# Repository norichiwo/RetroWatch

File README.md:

# RetroWatch

PCB file creation = KiCAD : Version: 8.0.1

Firmware creation = STM32CubeIDE : Version: 1.15.1

Details are shown in following blog pages ( Only in Japanese)

https://norichiwo.hatenablog.com/entry/2024/11/10/233512

https://norichiwo.hatenablog.com/entry/2024/11/17/223525

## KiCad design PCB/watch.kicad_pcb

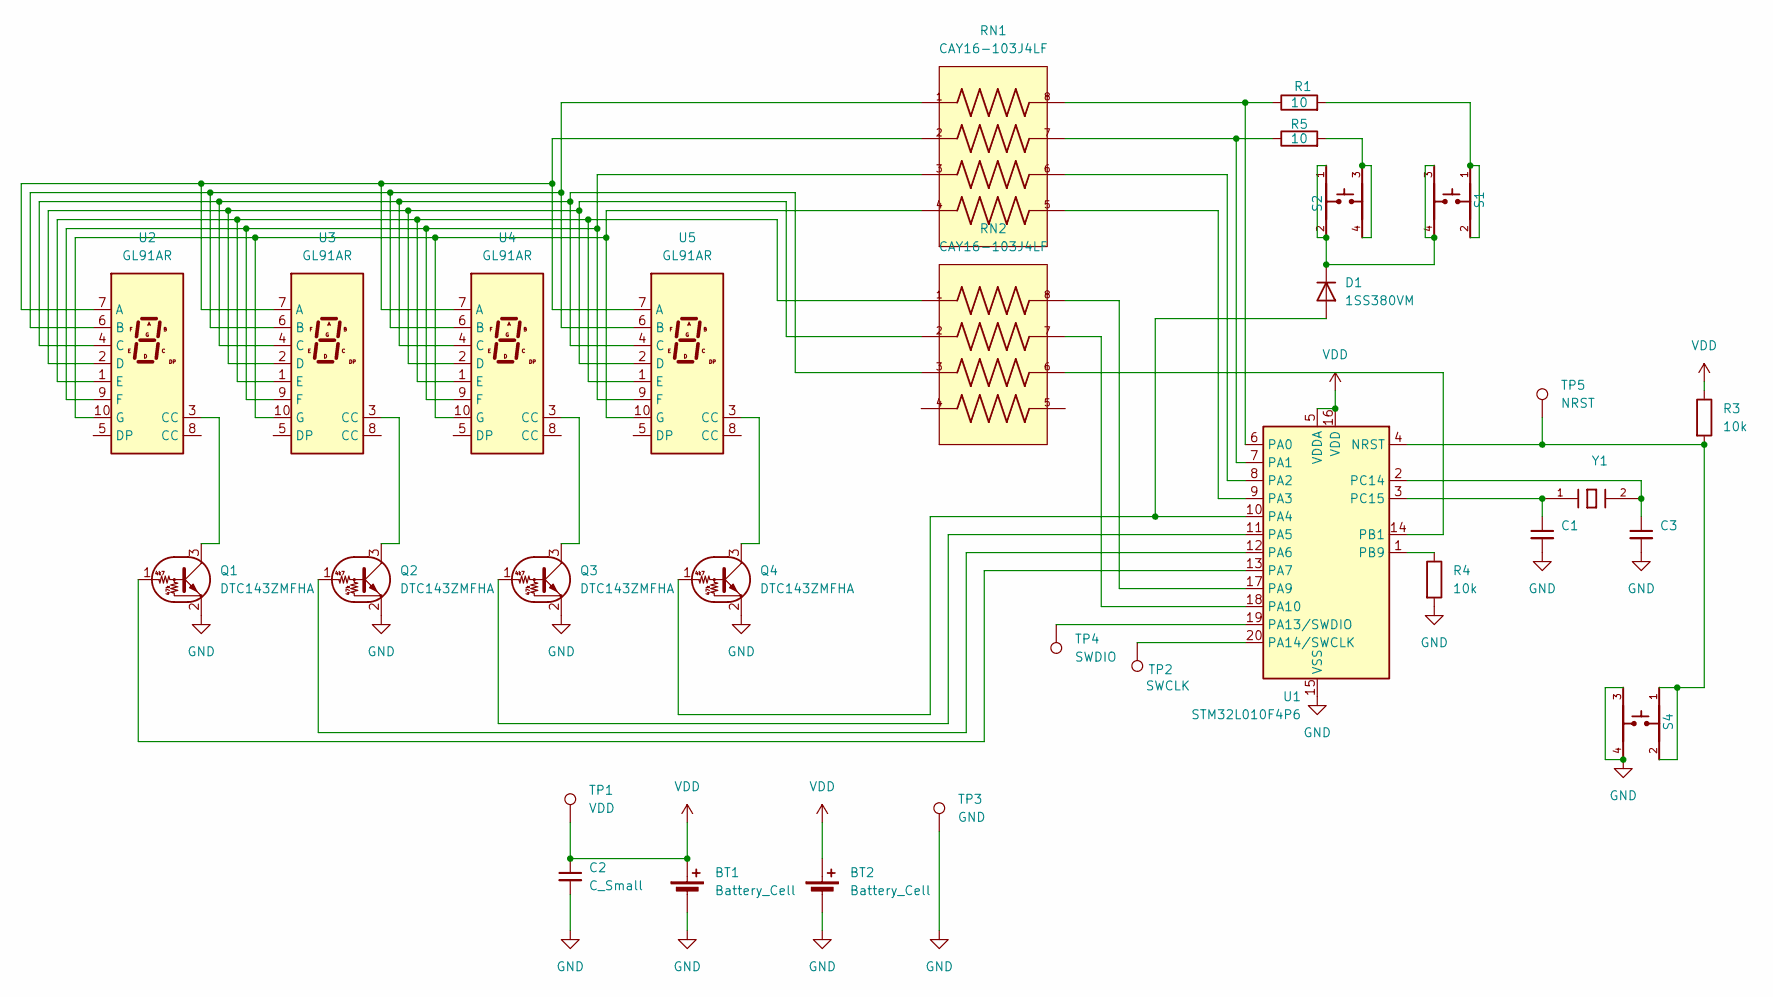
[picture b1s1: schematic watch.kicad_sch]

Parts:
BT1: Battery_Cell; BatteryHolder_Keystone_1058_1x2032
BT2: Battery_Cell; Battery_CH224-2032
C1, C2, C3: C_Small; C_0603_1608Metric
D1: 1SS380VM; D_SOD-323F
Q1, Q2, Q3, Q4: DTC143ZMFHA; SOT-723
R1, R5: 10; R_0603_1608Metric
R3, R4: 10k; R_0603_1608Metric
RN1, RN2: CAY16-103J4LF; RESCAF80P320X160X60-8N
S1, S2, S4: SKRPACE010; SW_SKRPACE010
TP1: VDD; TestPoint_THTPad_D1.1mm_Drill0.7mm
TP2: SWCLK; TestPoint_THTPad_D1.1mm_Drill0.7mm
TP3: GND; TestPoint_THTPad_D1.1mm_Drill0.7mm
TP4: SWDIO; TestPoint_THTPad_D1.1mm_Drill0.7mm
TP5: NRST; TestPoint_THTPad_D1.1mm_Drill0.7mm
U1: STM32L010F4P6; TSSOP-20_4.4x6.5mm_P0.65mm
U2, U3, U4, U5: GL91AR
Y1: FC-135_32.7680KA-A0; XTAL_FC-135_32.7680KA-A0

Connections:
GND: BT1.2 (-), BT2.2 (-), C1.2, C2.2, C3.2, Q1.2 (E), Q2.2 (E), Q3.2 (E), Q4.2 (E), R4.2, S4.3, S4.4, TP3.1, U1.15 (VSS)
unnamed: D1.2 (A), Q4.1 (B), U1.10 (PA4)
unnamed: D1.1 (K), S1.3, S1.4, S2.1, S2.2
unnamed: Q1.1 (B), U1.13 (PA7)
unnamed: Q1.3 (C), U2.3 (CC)
unnamed: Q2.1 (B), U1.12 (PA6)
unnamed: Q2.3 (C), U3.3 (CC)
unnamed: Q3.1 (B), U1.11 (PA5)
unnamed: Q3.3 (C), U4.3 (CC)
unnamed: Q4.3 (C), U5.3 (CC)
unnamed: R1.2, S1.1, S1.2
unnamed: R5.2, S2.3, S2.4
unnamed: R3.2, S4.1, S4.2, TP5.1, U1.4 (NRST)
unnamed: R1.1, RN1.8, U1.6 (PA0)
unnamed: R5.1, RN1.7, U1.7 (PA1)
unnamed: RN1.6, U1.8 (PA2)
unnamed: RN1.5, U1.9 (PA3)
unnamed: RN2.8, U1.17 (PA9)
unnamed: RN2.7, U1.18 (PA10)
unnamed: TP4.1, U1.19 (PA13/SWDIO)
unnamed: TP2.1, U1.20 (PA14/SWCLK)
unnamed: RN2.6, U1.14 (PB1)
unnamed: R4.1, U1.1 (PB9)
unnamed: C3.1, U1.2 (PC14), Y1.2
unnamed: C1.1, U1.3 (PC15), Y1.1
unnamed: RN1.2, U2.7 (A), U3.7 (A), U4.7 (A), U5.7 (A)
unnamed: RN1.1, U2.6 (B), U3.6 (B), U4.6 (B), U5.6 (B)
unnamed: RN2.3, U2.4 (C), U3.4 (C), U4.4 (C), U5.4 (C)
unnamed: RN2.2, U2.2 (D), U3.2 (D), U4.2 (D), U5.2 (D)
unnamed: RN2.1, U2.1 (E), U3.1 (E), U4.1 (E), U5.1 (E)
unnamed: RN1.3, U2.9 (F), U3.9 (F), U4.9 (F), U5.9 (F)
unnamed: RN1.4, U2.10 (G), U3.10 (G), U4.10 (G), U5.10 (G)
VDD: BT1.1 (+), BT2.1 (+), C2.1, R3.1, TP1.1, U1.5 (VDDA), U1.16 (VDD)

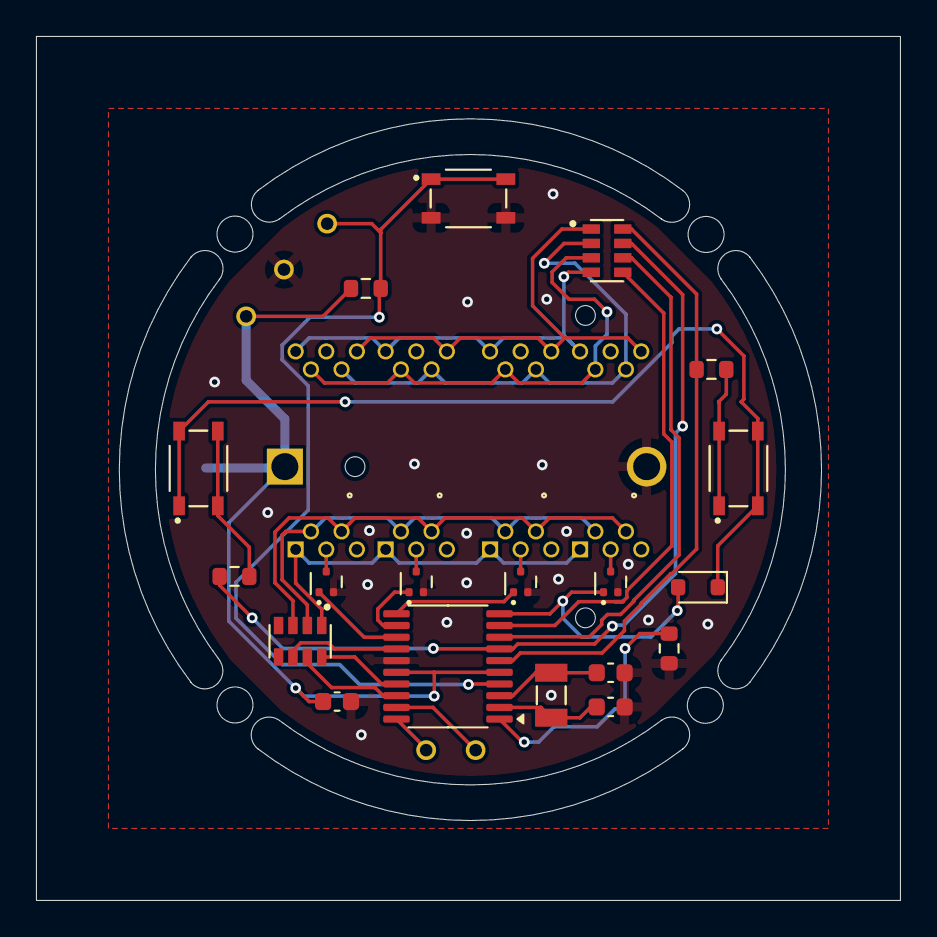
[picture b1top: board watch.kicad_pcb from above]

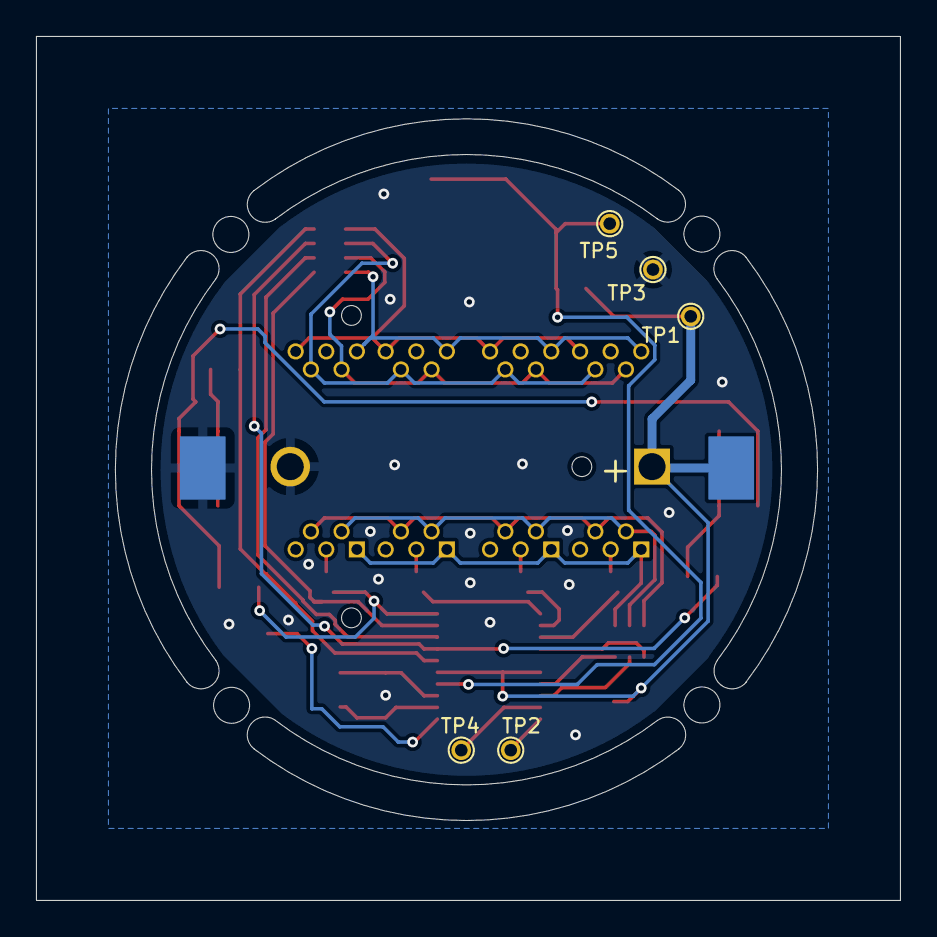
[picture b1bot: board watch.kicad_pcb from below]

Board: 2 copper layers, 48.0 x 48.0 mm, 30 parts (7 on the bottom side), 33 nets.

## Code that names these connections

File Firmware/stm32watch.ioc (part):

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Mcu.Name=STM32L010F4Px
Mcu.Package=TSSOP20
Mcu.UserName=STM32L010F4Px
PA0-CK_IN.GPIOParameters=GPIO_Speed,GPIO_PuPd,GPIO_Label,GPIO_ModeDefaultOutputPP
PA0-CK_IN.GPIO_Label=SEGB
PA0-CK_IN.GPIO_ModeDefaultOutputPP=GPIO_MODE_OUTPUT_PP
PA0-CK_IN.GPIO_PuPd=GPIO_NOPULL
PA0-CK_IN.GPIO_Speed=GPIO_SPEED_FREQ_LOW
PA0-CK_IN.Signal=GPIO_Output
PA1.GPIOParameters=GPIO_Speed,GPIO_Label
PA1.GPIO_Label=SEGA
PA1.GPIO_Speed=GPIO_SPEED_FREQ_LOW
PA1.Signal=GPIO_Output
PA10.GPIOParameters=GPIO_Label
PA10.GPIO_Label=SEGD
PA10.Signal=GPIO_Output
PA13.Mode=Serial_Wire
PA13.Signal=SYS_SWDIO
PA14.Mode=Serial_Wire
PA14.Signal=SYS_SWCLK
PA2.GPIOParameters=GPIO_Speed,GPIO_Label
PA2.GPIO_Label=SEGG
PA2.GPIO_Speed=GPIO_SPEED_FREQ_LOW
PA2.Signal=GPIO_Output
PA3.GPIOParameters=GPIO_Speed,GPIO_Label
PA3.GPIO_Label=SEGF
PA3.GPIO_Speed=GPIO_SPEED_FREQ_LOW
PA3.Signal=GPIO_Output
PA4.GPIOParameters=GPIO_Label
PA4.GPIO_Label=DIG0
PA4.Signal=GPIO_Output
PA5.GPIOParameters=GPIO_Label
PA5.GPIO_Label=DIG1
PA5.Signal=GPIO_Output
PA6.GPIOParameters=GPIO_Label
PA6.GPIO_Label=DIG2
PA6.Signal=GPIO_Output
PA7.GPIOParameters=GPIO_Label
PA7.GPIO_Label=DIG3
PA7.Signal=GPIO_Output
PA9.GPIOParameters=GPIO_Label
PA9.GPIO_Label=SEGE
PA9.Signal=GPIO_Output
PB1.GPIOParameters=GPIO_Label
PB1.GPIO_Label=SEGC
PB1.Signal=GPIO_Output
PC14-OSC32_IN.Mode=LSE-External-Oscillator
PC14-OSC32_IN.Signal=RCC_OSC32_IN
PC15-OSC32_OUT.Mode=LSE-External-Oscillator
PC15-OSC32_OUT.Signal=RCC_OSC32_OUT
RCC.HSE_VALUE=8000000
RCC.SYSCLKFreq_VALUE=4194000
board=custom

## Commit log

2024-12-08 Create test
2024-12-08 Create tes
